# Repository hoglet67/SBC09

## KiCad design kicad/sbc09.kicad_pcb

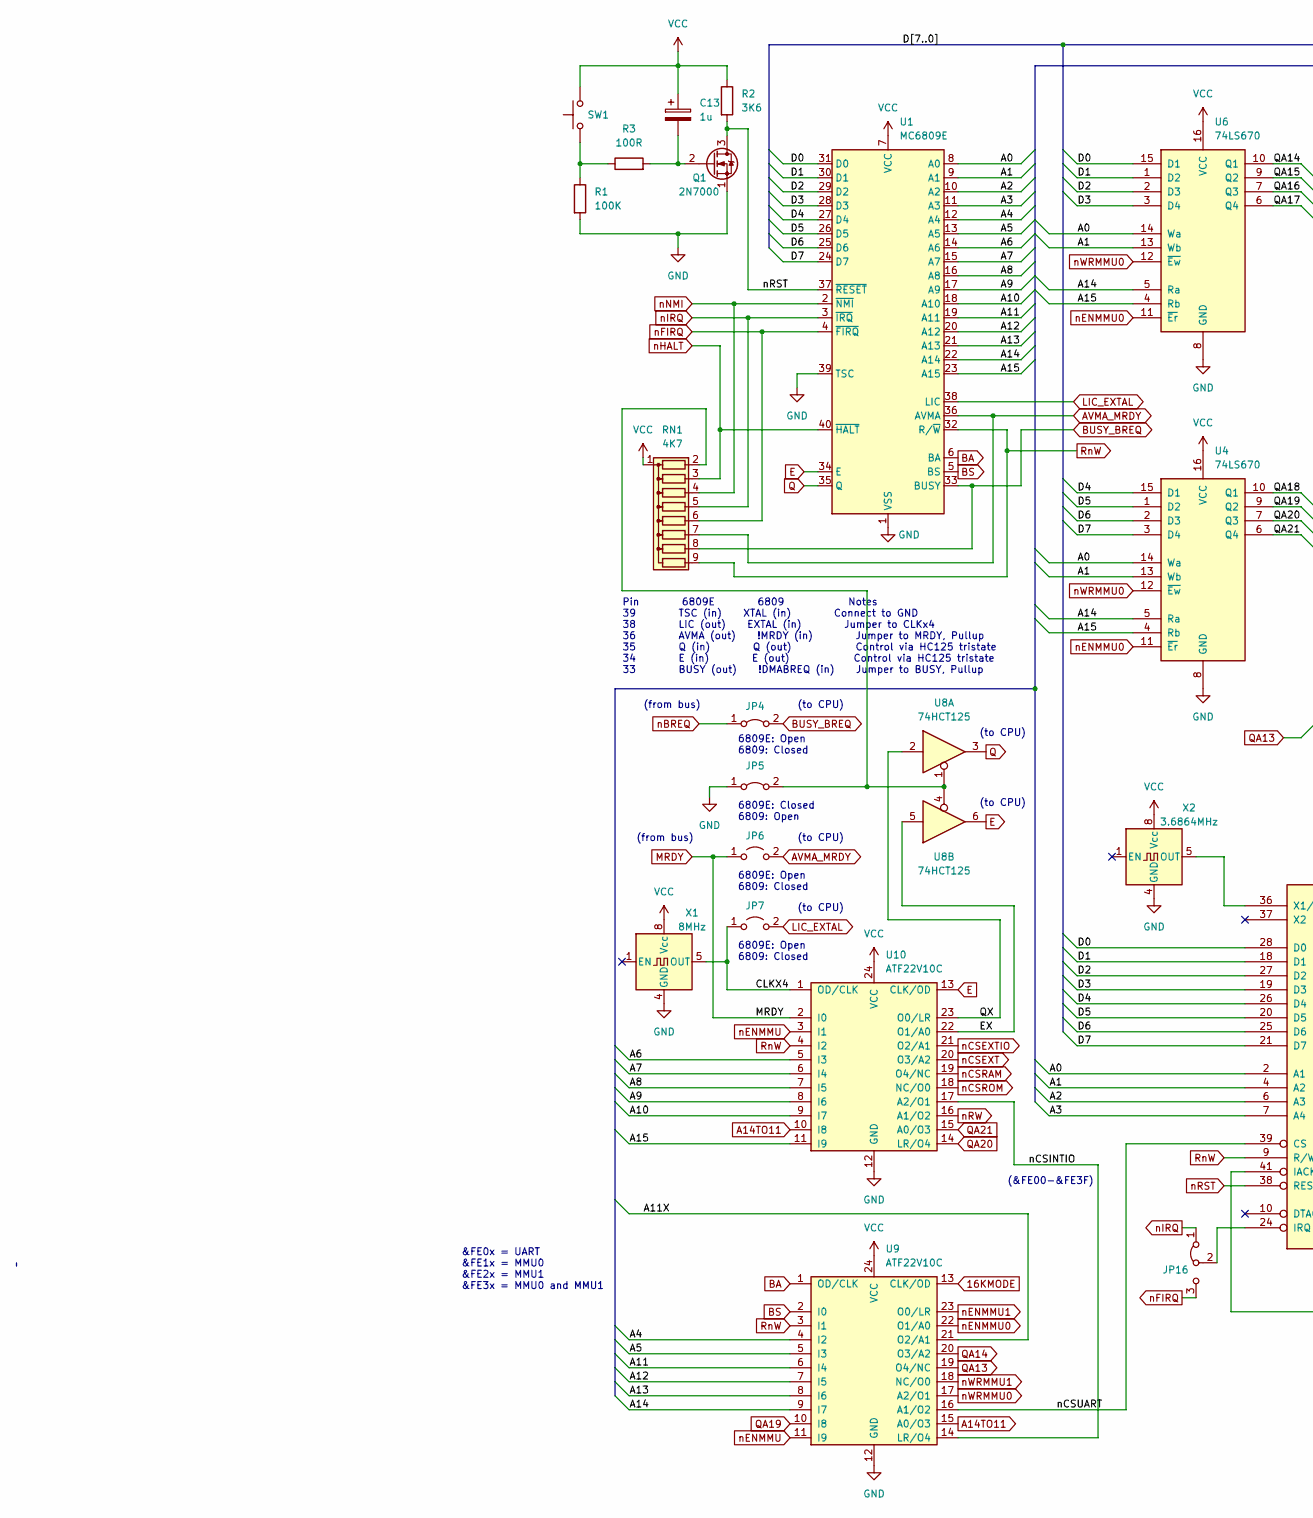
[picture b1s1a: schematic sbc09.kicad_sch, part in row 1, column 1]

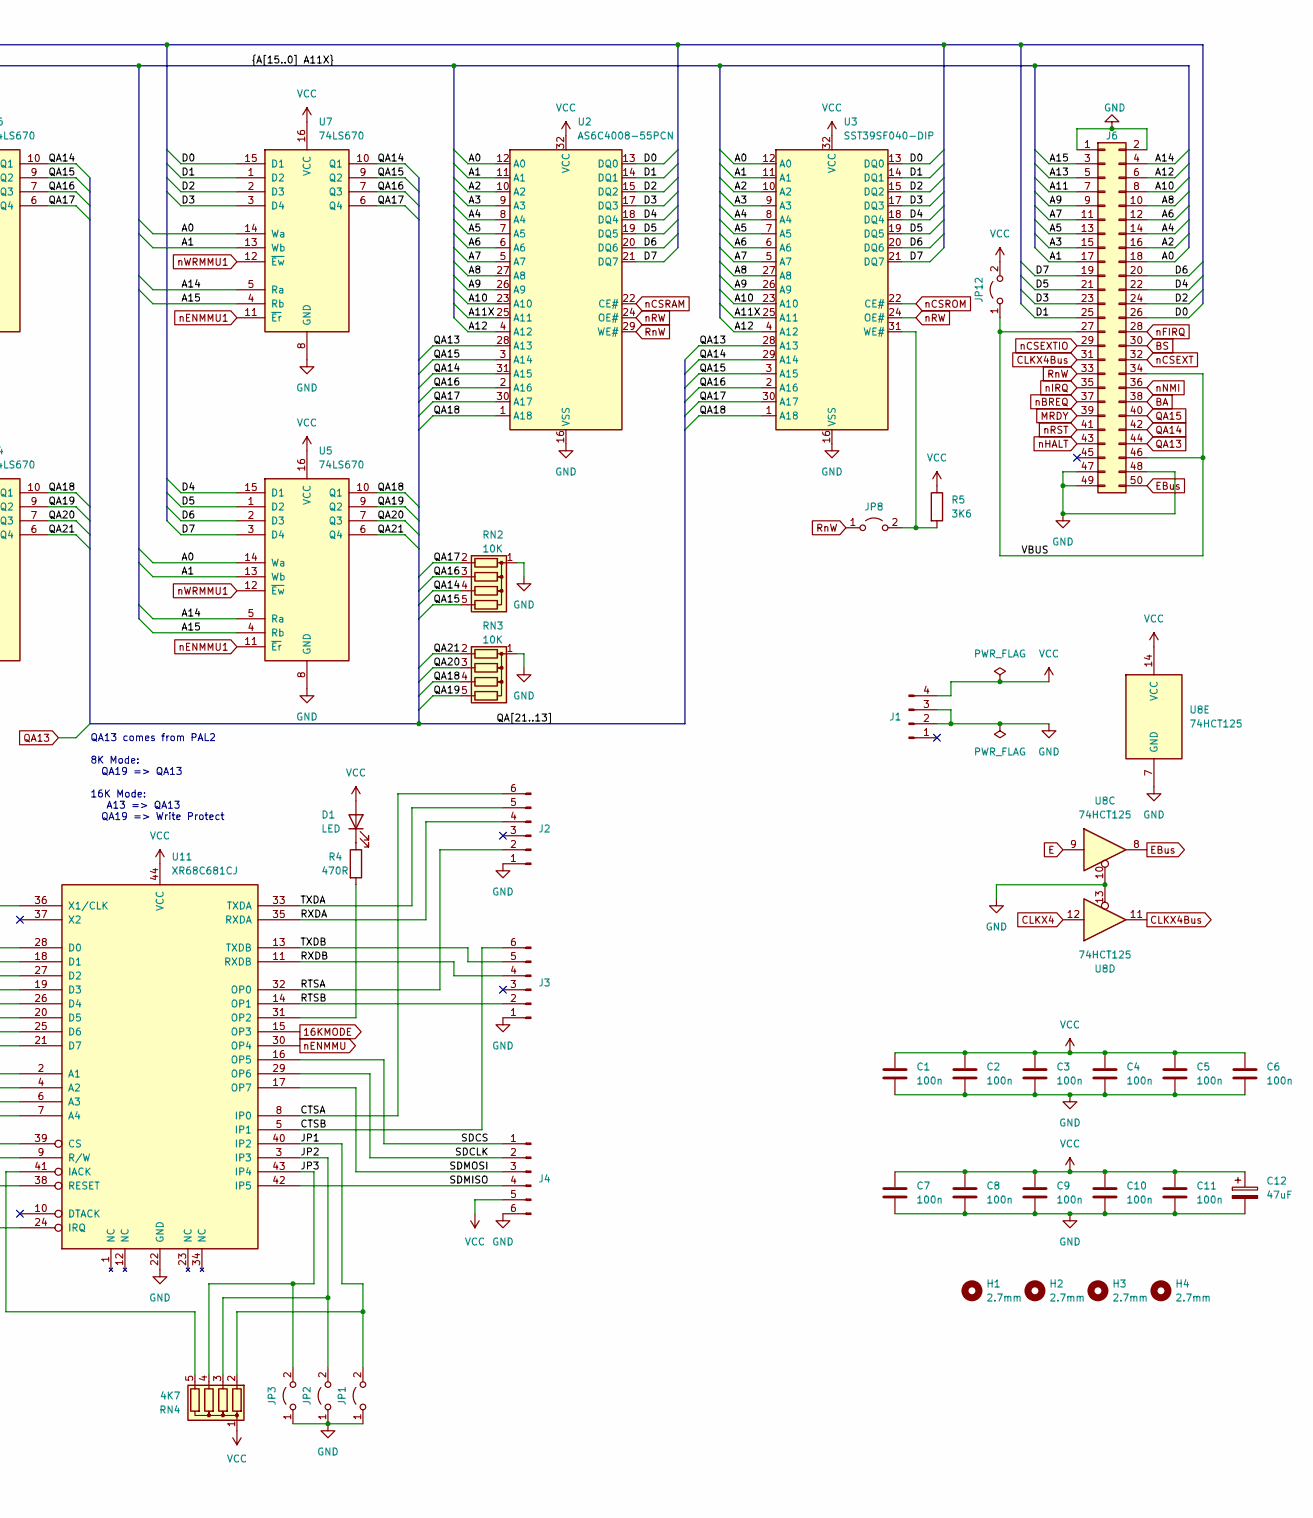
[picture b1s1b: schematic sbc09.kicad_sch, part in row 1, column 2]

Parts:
C1, C2, C3, C4, C5, C6, C7, C8, C9, C10, C11: 100n; C_Disc_D4.7mm_W2.5mm_P5.00mm
C12: 47uF; CP_Radial_D5.0mm_P2.50mm
C13: 1u; CP_Radial_D5.0mm_P2.50mm
D1: LED; LED_D3.0mm_Horizontal_O1.27mm_Z2.0mm
H1, H2, H3, H4: 2.7mm; MountingHole_2.7mm
J1: Conn_01x04_Male; Molex_KK-254_AE-6410-04A_1x04_P2.54mm_Vertical
J2, J3, J4: Conn_01x06_Male; PinSocket_1x06_P2.54mm_Horizontal
J6: Conn_02x25_Odd_Even; IDC-Header_2x25_P2.54mm_Horizontal
JP1, JP2, JP3, JP6, JP7, JP8, JP12: Jumper_2_Open; PinHeader_1x02_P2.54mm_Vertical
JP4, JP5: Jumper_2_Bridged; PinHeader_1x02_P2.54mm_Vertical
JP16: Jumper_3_Bridged12; PinHeader_1x03_P2.54mm_Vertical
Q1: 2N7000; TO-92_Inline
R1: 100K; R_Axial_DIN0207_L6.3mm_D2.5mm_P10.16mm_Horizontal
R2, R5: 3K6; R_Axial_DIN0207_L6.3mm_D2.5mm_P10.16mm_Horizontal
R3: 100R; R_Axial_DIN0207_L6.3mm_D2.5mm_P10.16mm_Horizontal
R4: 470R; R_Axial_DIN0207_L6.3mm_D2.5mm_P10.16mm_Horizontal
RN1: 4K7; R_Array_SIP9
RN2, RN3: 10K; R_Array_SIP5
RN4: 4K7; R_Array_SIP5
SW1: SW_Push; SW_Tactile_SPST_Angled_PTS645Vx83-2LFS
U1: MC6809E; DIP-40_W15.24mm_Socket
U2: AS6C4008-55PCN; DIP-32_W15.24mm_Socket
U3: SST39SF040-DIP; DIP-32_W15.24mm_Socket
U4, U5, U6, U7: 74LS670; DIP-16_W7.62mm_Socket
U8: 74HCT125; DIP-14_W7.62mm_Socket
U9, U10: ATF22V10C; DIP-24_W7.62mm_Socket
U11: XR68C681CJ; PLCC-44_THT-Socket
X1: 8MHz; Oscillator_DIP-8
X2: 3.6864MHz; Oscillator_DIP-8

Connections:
16KMODE: U9.13 (CLK/OD), U11.15 (OP3)
/A0: J6.18, U1.8 (A0), U2.12 (A0), U3.12 (A0), U4.14 (Wa), U5.14 (Wa), U6.14 (Wa), U7.14 (Wa), U11.2 (A1)
/A1: J6.17, U1.9 (A1), U2.11 (A1), U3.11 (A1), U4.13 (Wb), U5.13 (Wb), U6.13 (Wb), U7.13 (Wb), U11.4 (A2)
/A2: J6.16, U1.10 (A2), U2.10 (A2), U3.10 (A2), U11.6 (A3)
/A3: J6.15, U1.11 (A3), U2.9 (A3), U3.9 (A3), U11.7 (A4)
/A4: J6.14, U1.12 (A4), U2.8 (A4), U3.8 (A4), U9.4 (I2)
/A5: J6.13, U1.13 (A5), U2.7 (A5), U3.7 (A5), U9.5 (I3)
/A6: J6.12, U1.14 (A6), U2.6 (A6), U3.6 (A6), U10.5 (I3)
/A7: J6.11, U1.15 (A7), U2.5 (A7), U3.5 (A7), U10.6 (I4)
/A8: J6.10, U1.16 (A8), U2.27 (A8), U3.27 (A8), U10.7 (I5)
/A9: J6.9, U1.17 (A9), U2.26 (A9), U3.26 (A9), U10.8 (I6)
/A10: J6.8, U1.18 (A10), U2.23 (A10), U3.23 (A10), U10.9 (I7)
/A11: J6.7, U1.19 (A11), U9.6 (I4)
/A11X: U2.25 (A11), U3.25 (A11), U9.21 (O2/A1)
/A12: J6.6, U1.20 (A12), U2.4 (A12), U3.4 (A12), U9.7 (I5)
/A13: J6.5, U1.21 (A13), U9.8 (I6)
/A14: J6.4, U1.22 (A14), U4.5 (Ra), U5.5 (Ra), U6.5 (Ra), U7.5 (Ra), U9.9 (I7)
/A15: J6.3, U1.23 (A15), U4.4 (Rb), U5.4 (Rb), U6.4 (Rb), U7.4 (Rb), U10.11 (I9)
/CTSA: J2.6, U11.8 (IP0)
/CTSB: J3.6, U11.5 (IP1)
/D0: J6.26, U1.31 (D0), U2.13 (DQ0), U3.13 (DQ0), U6.15 (D1), U7.15 (D1), U11.28 (D0)
/D1: J6.25, U1.30 (D1), U2.14 (DQ1), U3.14 (DQ1), U6.1 (D2), U7.1 (D2), U11.18 (D1)
/D2: J6.24, U1.29 (D2), U2.15 (DQ2), U3.15 (DQ2), U6.2 (D3), U7.2 (D3), U11.27 (D2)
/D3: J6.23, U1.28 (D3), U2.17 (DQ3), U3.17 (DQ3), U6.3 (D4), U7.3 (D4), U11.19 (D3)
/D4: J6.22, U1.27 (D4), U2.18 (DQ4), U3.18 (DQ4), U4.15 (D1), U5.15 (D1), U11.26 (D4)
/D5: J6.21, U1.26 (D5), U2.19 (DQ5), U3.19 (DQ5), U4.1 (D2), U5.1 (D2), U11.20 (D5)
/D6: J6.20, U1.25 (D6), U2.20 (DQ6), U3.20 (DQ6), U4.2 (D3), U5.2 (D3), U11.25 (D6)
/D7: J6.19, U1.24 (D7), U2.21 (DQ7), U3.21 (DQ7), U4.3 (D4), U5.3 (D4), U11.21 (D7)
/EX: U8.5, U10.22 (O1/A0)
/JP1: JP1.2 (B), RN4.2 (R1), U11.40 (IP2)
/JP2: JP2.2 (B), RN4.3 (R2), U11.3 (IP3)
/JP3: JP3.2 (B), RN4.4 (R3), U11.43 (IP4)
/QA16: RN2.3 (R2), U2.2 (A16), U3.2 (A16), U6.7 (Q3), U7.7 (Q3)
/QA17: RN2.2 (R1), U2.30 (A17), U3.30 (A17), U6.6 (Q4), U7.6 (Q4)
/QA18: RN3.4 (R3), U2.1 (A18), U3.1 (A18), U4.10 (Q1), U5.10 (Q1)
/QX: U8.2, U10.23 (O0/LR)
/RTSA: J2.2, U11.32 (OP0)
/RTSB: J3.2, U11.14 (OP1)
/RXDA: J2.4, U11.35 (RXDA)
/RXDB: J3.4, U11.11 (RXDB)
/SDCLK: J4.2, U11.29 (OP6)
/SDCS: J4.1, U11.16 (OP5)
/SDMISO: J4.4, U11.42 (IP5)
/SDMOSI: J4.3, U11.17 (OP7)
/TXDA: J2.5, U11.33 (TXDA)
/TXDB: J3.5, U11.13 (TXDB)
/VBUS: J6.27, J6.34, J6.46, JP12.1 (A)
/nCSINTIO: U9.14 (LR/O4), U10.17 (A2/O1)
/nCSUART: U9.16 (A1/O2), U11.39 (CS)
A14TO11: U9.15 (A0/O3), U10.10 (I8)
AVMA_MRDY: JP6.2 (B), RN1.7 (R6), U1.36 (AVMA)
BA: J6.38, U1.6 (BA), U9.1 (OD/CLK)
BS: J6.30, U1.5 (BS), U9.2 (I0)
BUSY_BREQ: JP4.2 (B), RN1.8 (R7), U1.33 (BUSY)
CLKX4: JP7.1 (A), U8.12, U10.1 (OD/CLK), X1.5 (OUT)
CLKX4Bus: J6.31, U8.11
E: U1.34 (E), U8.6, U8.9, U10.13 (CLK/OD)
EBus: J6.50, U8.8
GND: C1.2, C2.2, C3.2, C4.2, C5.2, C6.2, C7.2, C8.2, C9.2, C10.2, C11.2, C12.2, J1.2, J1.3, J2.1, J3.1, J4.6, J6.1, J6.2, J6.47, J6.48, J6.49, JP1.1 (A), JP2.1 (A), JP3.1 (A), JP5.1 (A), Q1.1 (S), R1.2, RN2.1 (common), RN3.1 (common), U1.1 (VSS), U1.39 (TSC), U2.16 (VSS), U3.16 (VSS), U4.8 (GND), U5.8 (GND), U6.8 (GND), U7.8 (GND), U8.7 (GND), U8.10, U8.13, U9.12 (GND), U10.12 (GND), U11.22 (GND), X1.4 (GND), X2.4 (GND)
LIC_EXTAL: JP7.2 (B), U1.38 (LIC)
MRDY: J6.39, JP6.1 (A), U10.2 (I0)
unnamed: C13.2, Q1.2 (G), R3.2
unnamed: D1.1 (K), R4.1
unnamed: JP5.2 (B), RN1.2 (R1), U8.1, U8.4
unnamed: JP16.2 (C), U11.24 (IRQ)
unnamed: R1.1, R3.1, SW1.1
unnamed: R4.2, U11.31 (OP2)
unnamed: RN4.5 (R4), U11.41 (IACK)
unnamed: JP8.2 (B), R5.2, U3.31 (WE#)
unnamed: U11.36 (X1/CLK), X2.5 (OUT)
Q: U1.35 (Q), U8.3
QA13: J6.44, U2.28 (A13), U3.28 (A13), U9.19 (O4/NC)
QA14: J6.42, RN2.4 (R3), U2.31 (A15), U3.29 (A14), U6.10 (Q1), U7.10 (Q1), U9.20 (O3/A2)
QA15: J6.40, RN2.5 (R4), U2.3 (A14), U3.3 (A15), U6.9 (Q2), U7.9 (Q2)
QA19: RN3.5 (R4), U4.9 (Q2), U5.9 (Q2), U9.10 (I8)
QA20: RN3.3 (R2), U4.7 (Q3), U5.7 (Q3), U10.14 (LR/O4)
QA21: RN3.2 (R1), U4.6 (Q4), U5.6 (Q4), U10.15 (A0/O3)
RnW: J6.33, JP8.1 (A), RN1.9 (R8), U1.32 (R/~W), U2.29 (WE#), U9.3 (I1), U10.4 (I2), U11.9 (R/W)
VCC: C1.1, C2.1, C3.1, C4.1, C5.1, C6.1, C7.1, C8.1, C9.1, C10.1, C11.1, C12.1, C13.1, D1.2 (A), J1.4, J4.5, JP12.2 (B), R2.1, R5.1, RN1.1 (common), RN4.1 (common), SW1.2, U1.7 (VCC), U2.32 (VCC), U3.32 (VCC), U4.16 (VCC), U5.16 (VCC), U6.16 (VCC), U7.16 (VCC), U8.14 (VCC), U9.24 (VCC), U10.24 (VCC), U11.44 (VCC), X1.8 (Vcc), X2.8 (Vcc)
nBREQ: J6.37, JP4.1 (A)
nCSEXT: J6.32, U10.20 (O3/A2)
nCSEXTIO: J6.29, U10.21 (O2/A1)
nCSRAM: U2.22 (CE#), U10.19 (O4/NC)
nCSROM: U3.22 (CE#), U10.18 (NC/O0)
nENMMU: U9.11 (I9), U10.3 (I1), U11.30 (OP4)
nENMMU0: U4.11 (~Er), U6.11 (~Er), U9.22 (O1/A0)
nENMMU1: U5.11 (~Er), U7.11 (~Er), U9.23 (O0/LR)
nFIRQ: J6.28, JP16.3 (B), RN1.6 (R5), U1.4 (~FIRQ)
nHALT: J6.43, RN1.3 (R2), U1.40 (~HALT)
nIRQ: J6.35, JP16.1 (A), RN1.5 (R4), U1.3 (~IRQ)
nNMI: J6.36, RN1.4 (R3), U1.2 (~NMI)
nRST: J6.41, Q1.3 (D), R2.2, U1.37 (~RESET), U11.38 (RESET)
nRW: U2.24 (OE#), U3.24 (OE#), U10.16 (A1/O2)
nWRMMU0: U4.12 (~Ew), U6.12 (~Ew), U9.17 (A2/O1)
nWRMMU1: U5.12 (~Ew), U7.12 (~Ew), U9.18 (NC/O0)

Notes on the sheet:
6809E: Open 6809: Closed
QA13 comes from PAL2 8K Mode: QA19 => QA13 16K Mode: A13 => QA13 QA19 => Write Protect
(to CPU)
6809E: Closed 6809: Open
&FE0x = UART &FE1x = MMU0 &FE2x = MMU1 &FE3x = MMU0 and MMU1
(from bus)
(&FE00-&FE3F)
Pin 6809E 6809 Notes 39 TSC (in) XTAL (in) Connect to GND 38 LIC (out) EXTAL (in) Jumper to CLKx4 36 AVMA (out) !MRDY (in) Jumper to MRDY, Pullup 35 Q (in) Q (out) Control via HC125 tristate 34 E (in) E (out) Control via HC125 tristate 33 BUSY (out) !DMABREQ (in) Jumper to BUSY, Pullup
6809E: Open 6809: Closed

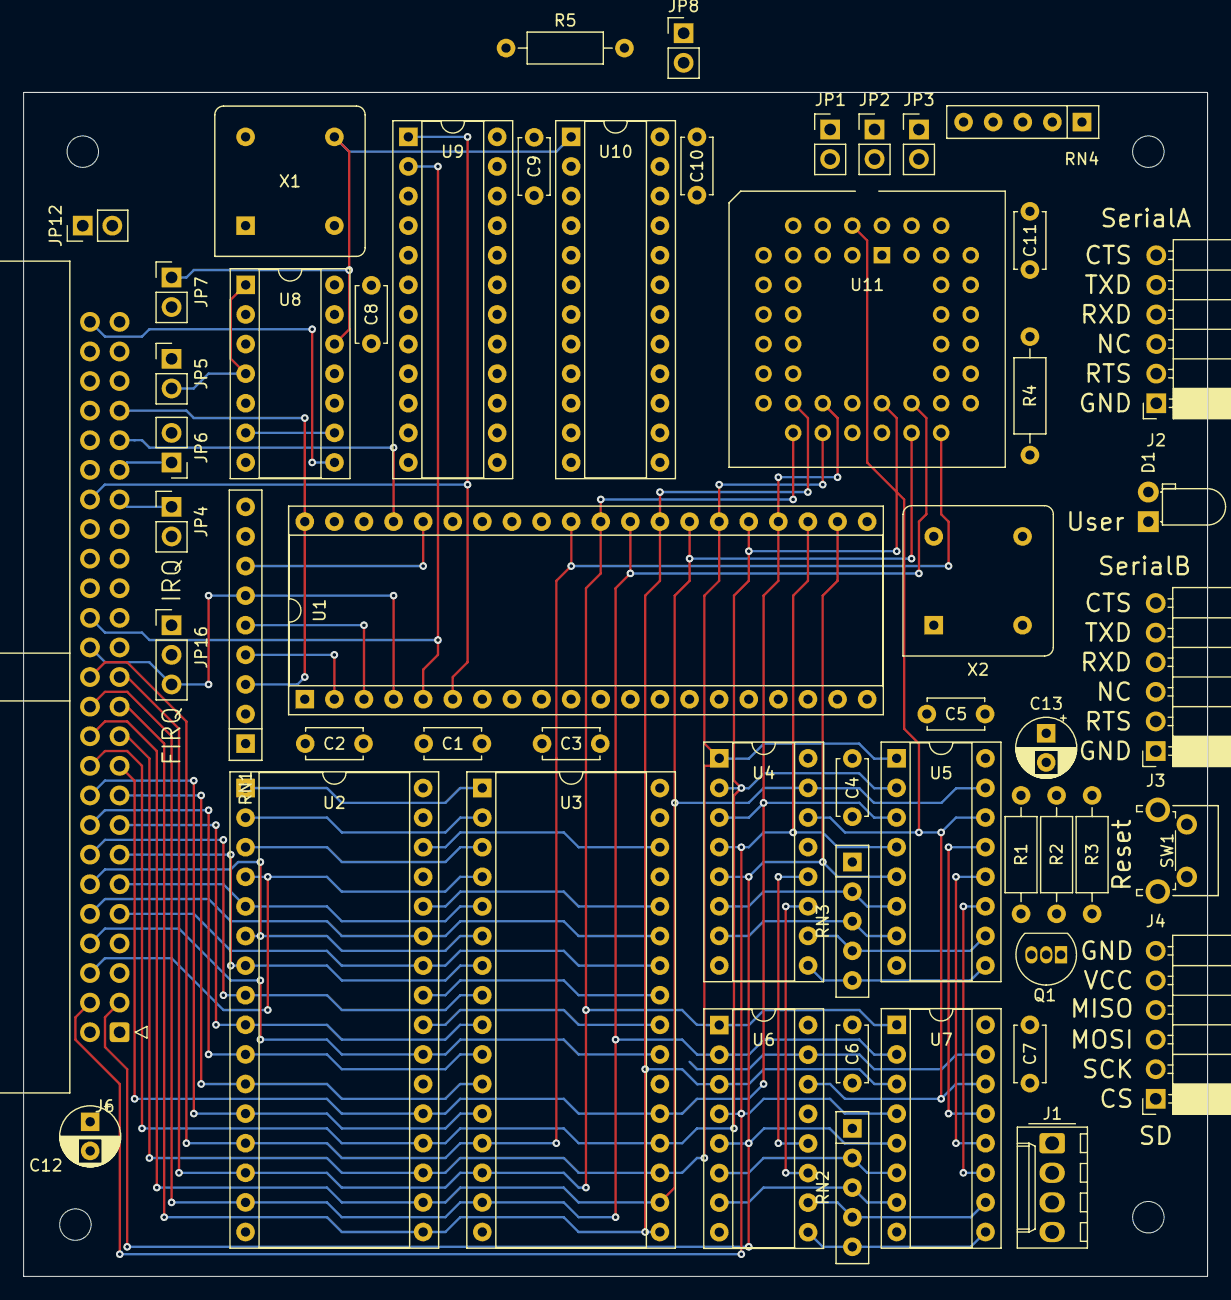
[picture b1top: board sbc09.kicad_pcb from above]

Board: 4 copper layers, 101.6 x 101.6 mm, 57 parts (0 on the bottom side), 95 nets.

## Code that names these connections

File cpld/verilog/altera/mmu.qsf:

# -------------------------------------------------------------------------- #
#
# Copyright (C) 1991-2013 Altera Corporation
# Your use of Altera Corporation's design tools, logic functions
# and other software and tools, and its AMPP partner logic
# functions, and any output files from any of the foregoing
# (including device programming or simulation files), and any
# associated documentation or information are expressly subject
# to the terms and conditions of the Altera Program License
# Subscription Agreement, Altera MegaCore Function License
# Agreement, or other applicable license agreement, including,
# without limitation, that your use is for the sole purpose of
# programming logic devices manufactured by Altera and sold by
# Altera or its authorized distributors.  Please refer to the
# applicable agreement for further details.
#
# -------------------------------------------------------------------------- #
#
# Quartus II 32-bit
# Version 13.0.1 Build 232 06/12/2013 Service Pack 1 SJ Web Edition
# Date created = 16:57:10  November 12, 2022
#
# -------------------------------------------------------------------------- #
#
# Notes:
#
# 1) The default values for assignments are stored in the file:
#		mmu_assignment_defaults.qdf
#    If this file doesn't exist, see file:
#		assignment_defaults.qdf
#
# 2) Altera recommends that you do not modify this file. This
#    file is updated automatically by the Quartus II software
#    and any changes you make may be lost or overwritten.
#
# -------------------------------------------------------------------------- #


set_global_assignment -name FAMILY MAX7000S
set_global_assignment -name DEVICE "EPM7128SLC84-7"
set_global_assignment -name TOP_LEVEL_ENTITY mmu
set_global_assignment -name ORIGINAL_QUARTUS_VERSION "13.0 SP1"
set_global_assignment -name PROJECT_CREATION_TIME_DATE "16:57:10  NOVEMBER 12, 2022"
set_global_assignment -name LAST_QUARTUS_VERSION "13.0 SP1"
set_global_assignment -name PROJECT_OUTPUT_DIRECTORY output_files
set_global_assignment -name DEVICE_FILTER_PACKAGE PLCC
set_global_assignment -name DEVICE_FILTER_PIN_COUNT 84
set_global_assignment -name DEVICE_FILTER_SPEED_GRADE 7
set_global_assignment -name ERROR_CHECK_FREQUENCY_DIVISOR "-1"
set_global_assignment -name MIN_CORE_JUNCTION_TEMP 0
set_global_assignment -name MAX_CORE_JUNCTION_TEMP 85
set_global_assignment -name EDA_SIMULATION_TOOL "ModelSim-Altera (VHDL)"
set_global_assignment -name EDA_OUTPUT_DATA_FORMAT VHDL -section_id eda_simulation
set_global_assignment -name VERILOG_FILE ../mmu.v
set_global_assignment -name VERILOG_FILE ../mmu_int.v
set_global_assignment -name MAX7000_OPTIMIZATION_TECHNIQUE AREA
set_global_assignment -name SYNTH_TIMING_DRIVEN_SYNTHESIS OFF
set_global_assignment -name MAX7000_DEVICE_IO_STANDARD TTL
set_location_assignment PIN_1 -to nRESET
set_location_assignment PIN_2 -to SPARE
set_location_assignment PIN_4 -to nCSEXT
set_location_assignment PIN_5 -to QX
set_location_assignment PIN_6 -to MRDY
set_location_assignment PIN_8 -to nCSROM0
set_location_assignment PIN_9 -to BUFDIR
set_location_assignment PIN_10 -to nCSEXTIO
set_location_assignment PIN_11 -to nBUFEN
set_location_assignment PIN_12 -to BS
set_location_assignment PIN_15 -to BA
set_location_assignment PIN_16 -to RnW
set_location_assignment PIN_17 -to ADDR[0]
set_location_assignment PIN_18 -to ADDR[1]
set_location_assignment PIN_20 -to ADDR[2]
set_location_assignment PIN_21 -to ADDR[3]
set_location_assignment PIN_22 -to ADDR[4]
set_location_assignment PIN_24 -to ADDR[5]
set_location_assignment PIN_25 -to ADDR[6]
set_location_assignment PIN_27 -to ADDR[7]
set_location_assignment PIN_28 -to ADDR[8]
set_location_assignment PIN_29 -to ADDR[9]
set_location_assignment PIN_30 -to ADDR[10]
set_location_assignment PIN_31 -to ADDR[11]
set_location_assignment PIN_33 -to ADDR[12]
set_location_assignment PIN_34 -to ADDR[13]
set_location_assignment PIN_35 -to ADDR[14]
set_location_assignment PIN_36 -to ADDR[15]
set_location_assignment PIN_37 -to DATA[0]
set_location_assignment PIN_39 -to DATA[1]
set_location_assignment PIN_40 -to DATA[2]
set_location_assignment PIN_41 -to DATA[3]
set_location_assignment PIN_44 -to DATA[4]
set_location_assignment PIN_45 -to DATA[5]
set_location_assignment PIN_46 -to DATA[6]
set_location_assignment PIN_48 -to DATA[7]
set_location_assignment PIN_49 -to nRW
set_location_assignment PIN_50 -to A11X
set_location_assignment PIN_51 -to QA13
set_location_assignment PIN_52 -to INTMASK
set_location_assignment PIN_54 -to MMU_DATA[4]
set_location_assignment PIN_55 -to MMU_DATA[3]
set_location_assignment PIN_56 -to MMU_DATA[5]
set_location_assignment PIN_57 -to MMU_DATA[2]
set_location_assignment PIN_58 -to MMU_DATA[1]
set_location_assignment PIN_60 -to MMU_DATA[0]
set_location_assignment PIN_61 -to MMU_DATA[6]
set_location_assignment PIN_63 -to MMU_DATA[7]
set_location_assignment PIN_64 -to MMU_ADDR[1]
set_location_assignment PIN_65 -to MMU_ADDR[0]
set_location_assignment PIN_67 -to MMU_ADDR[2]
set_location_assignment PIN_68 -to MMU_ADDR[3]
set_location_assignment PIN_69 -to MMU_nRD
set_location_assignment PIN_70 -to MMU_ADDR[4]
set_location_assignment PIN_73 -to SCLK
set_location_assignment PIN_74 -to MISO
set_location_assignment PIN_75 -to MMU_nWR
set_location_assignment PIN_76 -to MOSI
set_location_assignment PIN_77 -to nCSUART
set_location_assignment PIN_79 -to nCSROM1
set_location_assignment PIN_80 -to nCSRAM
set_location_assignment PIN_81 -to EX
set_location_assignment PIN_83 -to CLKX4
set_location_assignment PIN_84 -to ENCLK

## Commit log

2022-10-05 Added .gitignore
2022-10-05 Version with two 74LS670 and one 22V10
2022-10-05 Version with four 74LS670 and two 22V10
2022-10-07 Two oscillators, added QA13
2022-10-07 Use A14/15 instead of RA/RB
2022-10-07 QA13 generated by PAL
2022-10-12 Fix error in signals passed between PALs
2022-10-12 Try passing A12_A11_A10 between PALs
2022-10-12 Add wincupl binaries for convenience
2022-10-12 Added PALs (fitting issues in PAL2)
2022-10-12 Better partitioning of PALs
2022-10-12 Internal IO should be FE00-FE3F, not FC00-FC3F
2022-10-12 Started work on PCB
2022-10-13 Started manually routing the board
2022-10-14 100% Routed !!!
2022-10-14 Fix warnings
2022-10-14 Update IC references
2022-10-14 Changed Bus Connector from Female to Male
2022-10-14 Set min spacing to 8 mils and fixes a couple of minor violations
2022-10-15 Changed Bus Connector from Male back to Female
2022-10-15 Buffer E/Q on Bus
2022-10-15 Updated PDF Schematic
2022-10-24 Shrinking used space: work in progress
2022-10-24 Shrinking complete
2022-10-25 Tweak board placement; DIP-8 oscillators
2022-10-25 Minor
2022-10-25 Tweak board placement again to make gaps more even
2022-10-25 Messing with front panel connectors
2022-10-25 Moved LED to front panel
2022-10-25 Change board stackup to br 1.6mm
2022-10-25 OCD moving of decoupling caps
2022-10-25 OCD tweaking around MAX232E
2022-10-26 Moved reset components close to front panel
2022-10-26 Moved JP8 closer to JP4-7
2022-10-26 Started labelling
2022-10-26 Moved R3
2022-10-26 Name serial port nets
2022-10-26 Replaced 9-pin D-Sub with 10-pin header
2022-10-26 Replaced 2x5 header with polarized box header
2022-10-26 Move power connector
2022-10-28 Use 5mm pitch decoupling caps
2022-10-28 Make bus connector a MALE pin header
2022-10-28 Minor component movement around UART
2022-10-30 Remove loop in D3
2022-10-31 PAL2: Push negation into pins (same jedec fusemap)
2022-10-31 PAL2: Select devices based to A15/A14 when MMU disabled
2022-10-31 PAL1: Push negation into pins (same jedec fusemap)
2022-10-31 PAL1: Fix incorrectly named A8X output
2022-10-31 PAL2: Swap CSxxx select pins
2022-10-31 KiCAD: Swap CSxxx select pins
2022-10-31 PAL2: A14->QA14 when MMU disabled
2022-10-31 KiCAD: Route QA14 to spare PAL2 input
2022-10-31 PALs: Added latest doc and jed files
2022-11-03 Rename QA inputs (cosmetic, JEDEC unchanged)
2022-11-03 Test: Simple MMU test for 8K Mode
2022-11-03 PCB: Change order of QA19/20/21
2022-11-03 Added JP17 to select between IRQ and FIRQ for the UART interrupt
2022-11-03 Added pullup to RnW so it doesn't float during SYNC
2022-11-03 Labelling and move JP8
2022-11-03 Remove JP8 (caused fast clock stub) and renumbered remaining JPs
2022-11-03 Replace J1 (ext power) with Molex KK
2022-11-03 Control direction of Addr buffers from BA
2022-11-03 Change value of U1/2/3 to 74HCT245
2022-11-03 PAL1: tristate A8X when BA=1
2022-11-03 Correct comment on schematic
2022-11-07 Updated PDF
2022-11-07 PALs: Added PAL3 and refactored
2022-11-07 KiCAD: Added PAL3 and updated layout
2022-11-07 PALs: Update PAL1 to allow nCSUART to be later on UART writes
2022-11-07 KiCAD - tidy up schematic
2022-11-07 PALs: Sync pinouts with schematics
2022-11-07 Updated PDF (three pal design)
2022-11-07 Changes to support remote bus mastering
2022-11-07 Added Mouser BOM
2022-11-07 User -7 PALs as they are more available
2022-11-08 Remove unconnected track in schematic
2022-11-11 PALS: Seperate nBUFEN from nCSEXT
2022-11-11 Reroute several signals around PALs
2022-11-11 Connect A8 to bus address (not A8X)
2022-11-14 Started replacing PALs with CPLD
2022-11-15 CPLD pinout firmed up
2022-11-15 Verilog for MMU with external MMU RAM
2022-11-15 Verilog for MMU with 16x6 internal MMU RAM (won't fit)
2022-11-15 CPLD version now fully routed
2022-11-21 KiCAD: Change some global labels to outputs (cosmetic)
2022-11-21 MMU: Merge Dominic's changes from auto_task_switch_ed in sbc09_vunit_test repo
2022-11-21 MMU: Remove superfluous assignment
2022-11-21 MMU: Update Altera project with A8X->A11X change
2022-11-21 MMU: Make bidirectional IOs compatible with Yosys's limited support
2022-11-21 MMU: Add pin assignments into Verilog for convenience
2022-11-21 KiCAD: Remap A11 rather than A8 on vector fetch
2022-11-22 Added manual translation to CUPL for reference
2022-11-27 CPLD: Bit tidy up of build file; now just a cupl and verilog version
2022-11-27 CPLD: Add mCSEXTIO signal, and move MRDY
2022-11-27 Verilog CPLD: Introduce more variables (design unchanged)
2022-11-27 Verilog CPLD: Change S to U (saves one pt)
2022-11-27 Verilog CPLD: Correct polarity of nBUFEN
2022-11-27 Verilog CPLD: Make data out mux more efficient (saves 6 pts)
2022-11-27 KiCAD: Move MRDY and Add nCSEXTIO
2022-11-27 CUPL CPLD: Cosmetic
2022-11-27 CUPL CPLD: For now, exclude &FCxx and &FDxx from IO Space
2022-11-28 Verilog CPLD: Inclide &FCxx and &FDxx in IO Space
2022-11-29 Verilog CPLD: Added protect bit
2022-11-29 Verilog CPLD: Compressed reduced MMU down to 16 bytes of address space
2022-11-29 Verilog CPLD: Split into mmu and mmu_int
2022-12-01 KiCAD: Update PDF version of schematic
2022-12-03 Verilog CPLD: Fix Altera Project after refactor
2022-12-03 Verilog CPLD: Remove duplicate pin assigmnent section
2022-12-03 Verilog CPLD: Eliminate the use of ADDR[3]
2022-12-03 Verilog CPLD: Update wrapper to exclude ADDR3
2022-12-03 Verilog CPLD: Add INTMASK output and a 2-bit counter
2022-12-03 Verilog CPLD: Add nENCLK input and tristate EX/QX
2022-12-03 KiCAD: Replace 74HCT125 with 74HCT32 and add INTMASK from CPLD
2022-12-03 Verilog CPLD: Update Altera project with ENMMU and INTMASK
2022-12-06 Verilog CPLD: Correct MMU_DATA_out when MMU disabled
2022-12-18 Added simple boot ROM for Fuzix
2023-01-01 Verilog CPLD: Added simple SPI Master for SD Card
2023-01-01 Hack to allow nCSxx to be gated with E
2023-01-02 KiCAD: Connect SD Card to CPLD
2023-01-02 Verilog CPLD: Re-instate ADDR3 at the expense of seperate nRD/nWR signals
2023-01-02 KiCAD: Re-instate ADDR3 at the expense of seperate nRD/nWR signals
2023-01-02 Verilog CPLD: Merge E and EX clocks
2023-01-02 KiCAD: Merge E and EX clocks, add JP16 for spare input
2023-01-02 KiCAD: Split VCC/VCCBUS and redraw planes
2023-01-02 KiCAD: Add jumper inline with CPLD pin 84 for 12V injection
2023-01-02 KiCAD: Add jumper to isolate ROMs from RnW
2023-01-02 KiCAD: Connect QA13/14/15 to spare pins on the backplane connector (review assignments)
2023-01-02 KiCAD: Use solder jumpers to ground extra MMU address lines
2023-01-10 KiCAD: Added three resistors suggested by dp11
2023-04-15 KiCAD: Swap pins 6 and 84 on CPLD so nCLKEN on GOE1
2023-04-15 KiCAD: Make ENCLK active high
2023-04-15 KiCAD: Added JP4 jumper for XR68C681 input
2023-04-15 KiCAD: Block jumpers for IP2-5 and OP2-5
2023-04-15 KiCAD: Moved XC68C681 down by 0.05
2023-04-16 Verilog CPLD: Minor changes to EX/QX tristate (inc pinout)
2023-04-16 Verilog CPLD: refresh altera project with latest pinout
2023-04-16 CUPL CPLD: start bringing this back in sync with the Verilog project
2023-04-16 KiCAD: cost reducing
2023-04-19 KiCAD: more work...
2023-04-20 KiCAD: kill some vias
2023-04-21 Updated PALs for new logic partitioning
2023-04-21 Renumber jumpers
2023-04-21 Move RN2/3 up, silk screen
2023-04-21 Silk screen
2023-04-21 Correct SD card connections to UART
2023-04-21 Added PLCC socket and DIP packages to 3D model
2023-04-21 Cosmetic + update PDF
2023-04-22 Fix couple of errors in PALs
2023-04-22 Add RC filter for E going into PAL
2023-04-22 Update PDF schematic
2023-04-22 First attempt at manufacturing output
2023-04-22 Move C4 and C6 slightly
2023-04-22 Added jumper for power from SerialA
2023-05-05 Added JP12 (for 28L92 option) and route LIC to edge connector
2023-06-14 Update reset to use MCP100
2023-06-14 Swap couple of refs; set solder mask clarance / min width
2023-06-14 Update thermal releif params to 12mil spacing 16mil width
2023-06-14 Thicken up a Vbus connection
2023-06-14 Optimiise pads on inner layers
2023-06-14 Silkscreen only
2023-06-15 Final checks
2023-06-15 Added manufacturing files
2023-07-07 document memory map for 2 PAL version
2023-07-07 more Q's
2023-07-08 Some A's for Dominic
